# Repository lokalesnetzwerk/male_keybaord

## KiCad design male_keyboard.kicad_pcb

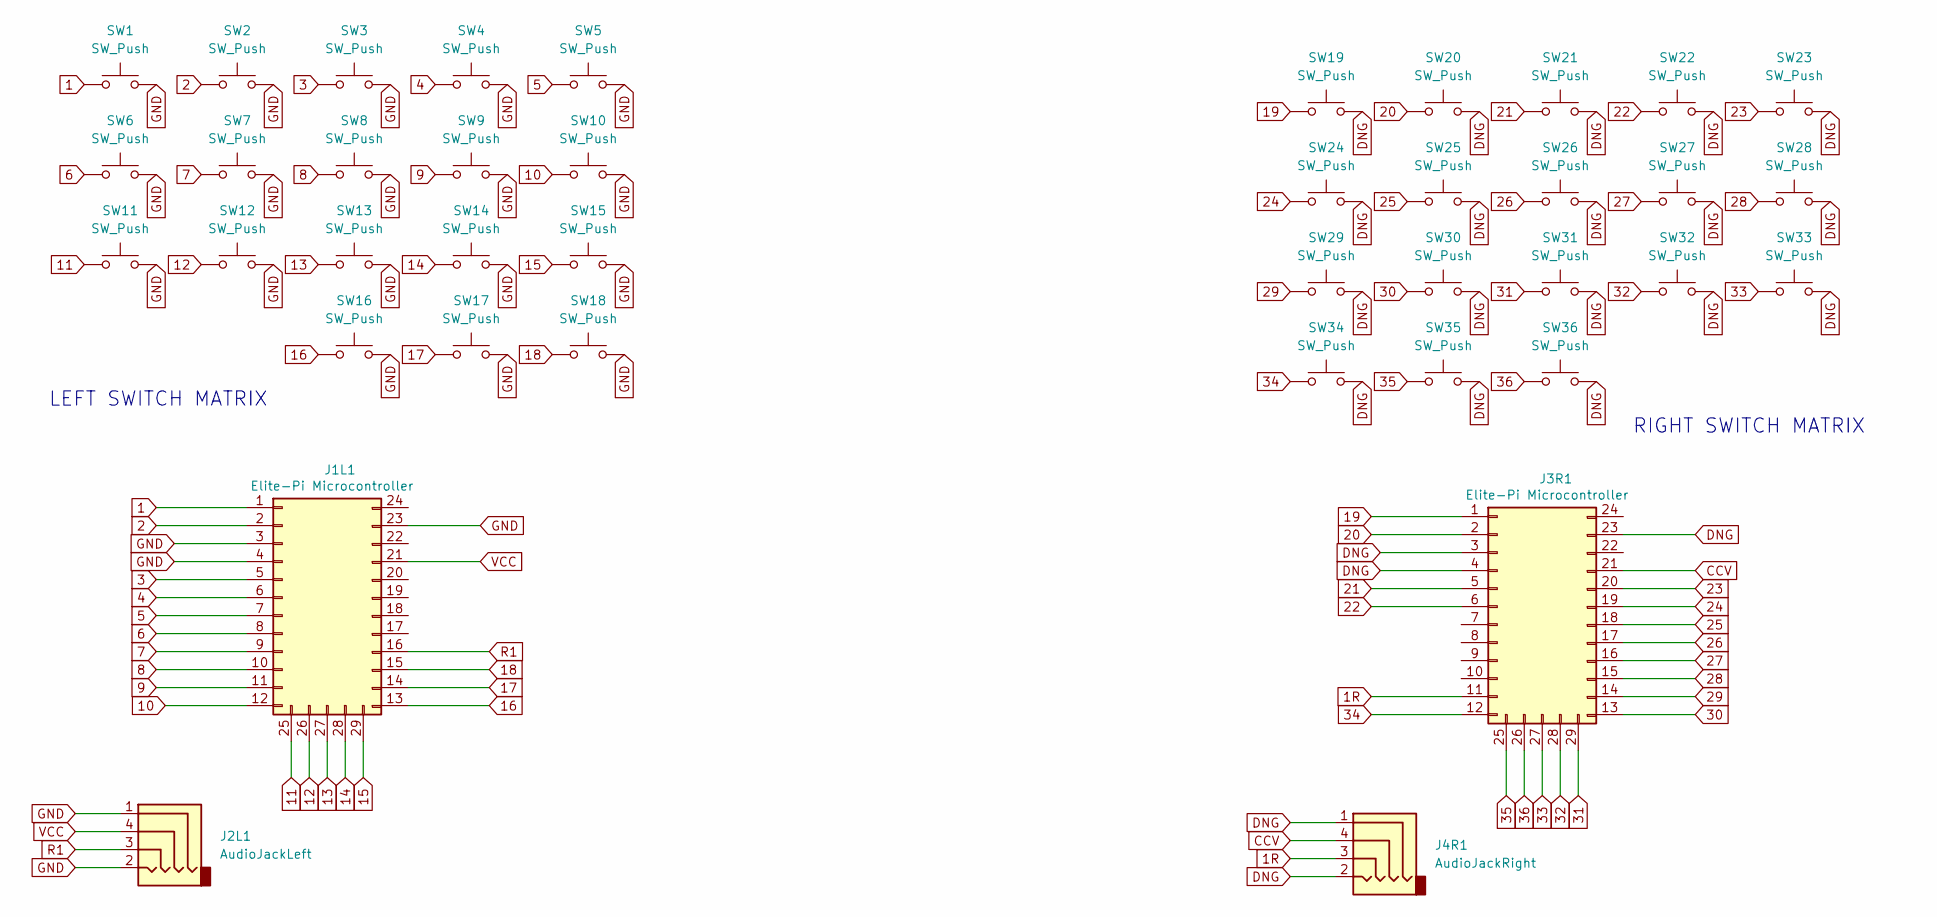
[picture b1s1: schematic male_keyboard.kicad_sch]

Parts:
J1L1, J3R1: Elite-Pi Microcontroller; Elite-C
J2L1: AudioJackLeft; TRRS-PJ-320A
J4R1: AudioJackRight; TRRS-PJ-320A
SW1, SW2, SW3, SW4, SW5, SW6, SW7, SW8, SW9, SW10, SW11, SW12, SW13, SW14, SW15, SW16, SW17, SW18, SW19, SW20, SW21, SW22, SW23, SW24, SW25, SW26, SW27, SW28, SW29, SW30, SW31, SW32, SW33, SW34, SW35, SW36: SW_Push; SW_Cherry_MX_1.00u_PCB

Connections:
1: J1L1.1, SW1.1
1R: J3R1.11, J4R1.3
2: J1L1.2, SW2.1
3: J1L1.5, SW3.1
4: J1L1.6, SW4.1
5: J1L1.7, SW5.1
6: J1L1.8, SW6.1
7: J1L1.9, SW7.1
8: J1L1.10, SW8.1
9: J1L1.11, SW9.1
10: J1L1.12, SW10.1
11: J1L1.25, SW11.1
12: J1L1.26, SW12.1
13: J1L1.27, SW13.1
14: J1L1.28, SW14.1
15: J1L1.29, SW15.1
16: J1L1.13, SW16.1
17: J1L1.14, SW17.1
18: J1L1.15, SW18.1
19: J3R1.1, SW19.1
20: J3R1.2, SW20.1
21: J3R1.5, SW21.1
22: J3R1.6, SW22.1
23: J3R1.20, SW23.1
24: J3R1.19, SW24.1
25: J3R1.18, SW25.1
26: J3R1.17, SW26.1
27: J3R1.16, SW27.1
28: J3R1.15, SW28.1
29: J3R1.14, SW29.1
30: J3R1.13, SW30.1
31: J3R1.29, SW31.1
32: J3R1.28, SW32.1
33: J3R1.27, SW33.1
34: J3R1.12, SW34.1
35: J3R1.25, SW35.1
36: J3R1.26, SW36.1
CCV: J3R1.21, J4R1.4
DNG: J3R1.3, J3R1.4, J3R1.23, J4R1.1, J4R1.2, SW19.2, SW20.2, SW21.2, SW22.2, SW23.2, SW24.2, SW25.2, SW26.2, SW27.2, SW28.2, SW29.2, SW30.2, SW31.2, SW32.2, SW33.2, SW34.2, SW35.2, SW36.2
GND: J1L1.3, J1L1.4, J1L1.23, J2L1.1, J2L1.2, SW1.2, SW2.2, SW3.2, SW4.2, SW5.2, SW6.2, SW7.2, SW8.2, SW9.2, SW10.2, SW11.2, SW12.2, SW13.2, SW14.2, SW15.2, SW16.2, SW17.2, SW18.2
R1: J1L1.16, J2L1.3
VCC: J1L1.21, J2L1.4

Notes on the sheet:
LEFT SWITCH MATRIX
RIGHT SWITCH MATRIX

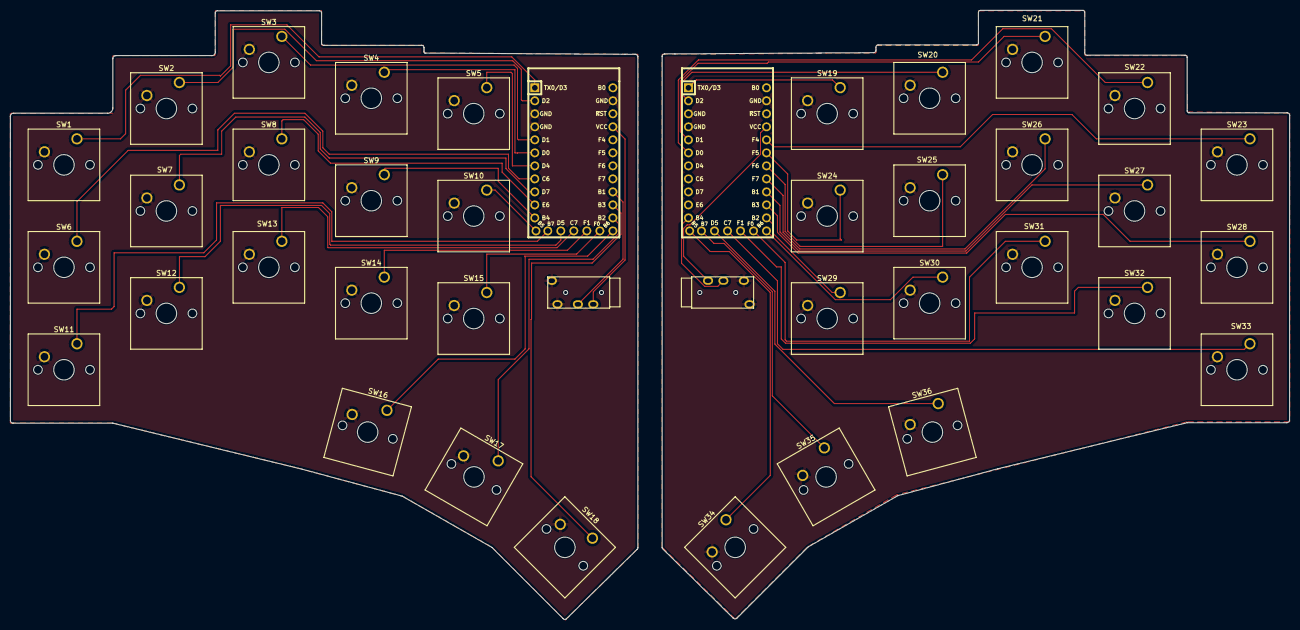
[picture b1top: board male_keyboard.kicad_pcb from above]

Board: 2 copper layers, 249.7 x 118.9 mm, 40 parts (0 on the bottom side), 42 nets.

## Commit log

2025-03-06 lennart und max sind males
2025-03-06 add submodules
2025-03-06 add symbols and footprints
2025-03-06 add kleeb submodule
2025-04-03 03042025
2025-04-15 15042025
2025-04-15 1504202502
2025-04-15 Copy DASBOB matrix
2025-04-15 1504202503
2025-04-15 left side footprints
2025-04-15 Label controller
2025-04-24 Add Keebio-Parts footprint submodule
2025-04-24 sort pcb
2025-04-24 fix number of switches and positions
2025-04-24 add gitignore
2025-04-24 Remove backups
2025-05-01 01052025
2025-05-01 fix left side references
2025-05-01 right side references
2025-05-01 order right side
2025-05-01 positioning right
2025-05-01 finish locking
2025-05-02 add ground plate and wires
2025-07-17 unknown changes
2025-07-17 two rounded corners
2025-07-20 rounded edges
